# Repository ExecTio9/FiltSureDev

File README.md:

# FiltSure HVAC Monitor

*Internal Project — FiltSure Team*

FiltSure is an IoT-based environmental monitoring system for HVAC systems. It collects real-time environmental data and filter identity information, logging to a cloud service via dual WiFi and LoRa communication.  
The system is designed for reliable field operation and simple installation by HVAC technicians or homeowners.

---

## System Overview

- 📡 Dual Communication: **WiFi** with **LoRa fallback**
- 🌡️ Tracks **Temperature**, **Humidity**, **Pressure**
- 🪪 Identifies Filters via **RFID**
- 🔋 Logs **Battery Voltage** and **Wind Speed**
- 🟢 Displays system health via **RGB LED Diagnostics**
- 🛠️ Designed for **easy installation** inside HVAC units

---

## Architecture

Sensors → ESP32 Sensor Node → WiFi / LoRa → ESP32 Hotspot Gateway → Google Apps Script → Google Sheets (Cloud Logging)

### Sensor Node

- **ESP32-C6 DevKitM-1**
- **BME280** — Temp / Humidity / Pressure
- **MFRC522** — RFID Filter Sensor
- **14-bit ADC** — Battery Monitor
- **12V Brushless Fan** — Wind Speed Sensor
- **RFM95** — LoRa Module
- **RGB LED** — Diagnostics
- **USB** — Power & Diagnostics Mode

### Gateway Node

- **ESP32-C3 or C6**
- **WiFi AP (ESP32 Hotspot)**
- **LoRa Receiver (RFM95)**
- **Google Apps Script Forwarding**
- **Diagnostic Ping Capability**

---

## Suggested Repo Structure

```text
FiltSure-HVAC-Monitor/
├── README.md                 # Project documentation (this file)
├── LICENSE.md                # Internal License
├── docs/                     # Architecture diagrams, setup guides
├── firmware/
│   ├── sensor_node/          # Source code for Sensor Node (ESP32-C6)
│   │   ├── src/
│   │   ├── include/
│   │   ├── platformio.ini    # or arduino config
│   ├── gateway_node/         # Source code for Gateway Node (ESP32-C3/C6)
│   │   ├── src/
│   │   ├── include/
│   │   ├── platformio.ini    # or arduino config
├── google_scripts/           # Google Apps Script for cloud logging
├── hardware/                 # Schematics, PCB files (KiCad)
├── testing/                  # Test scripts, diagnostic tools
└── images/                   # Project images, architecture diagrams

```
Data Fields

| Field             | Description               |
| ----------------- | ------------------------- |
| `id`              | Device ID                 |
| `boot count`      | Power cycle count         |
| `battery voltage` | Battery level (V)         |
| `sensor status`   | Sensor health status      |
| `temperature`     | Temperature in °C         |
| `humidity`        | Relative Humidity (%)     |
| `pressure`        | Pressure (hPa)            |
| `wind speed`      | Derived air flow velocity |
| `rfid`            | Filter RFID Tag UID       |

### Installation Guide For Technicians
- Mount Sensor Node inside HVAC unit (side wall recommended).
- Install Wind Sensor across airflow path.
- Attach RFID Tag to HVAC filter.
- Power the Node via battery or USB.
- Verify Gateway Connection (WiFi pairing).
- Confirm Data Logging in the FiltSure Google Sheet.

### Maintenance
- Replace battery pack periodically (check logged voltage).
- Trigger Diagnostic Mode when servicing units.
- OTA firmware updates via Gateway (WIP).

### Developer Setup
- Prerequisites
  - Arduino IDE or PlatformIO
  - ESP32 Board Support (ESP32-C3, C6)
- Required Libraries:
  - Adafruit_BME280
  - MFRC522
  - RadioHead (RH_RF95)
  - WiFiManager (if used)
  - Google Apps Script URL configured

## Flashing the Node
esptool.py --port COMx --baud 460800 write_flash 0x10000 firmware.bin

## Configuration
Edit these parameters in your code:
```text
#define WIFI_SSID     "ESP32_HOTSPOT"
#define WIFI_PASS     "FiltSure_Rules"
#define RF95_FREQ     915.0
#define NODE_ID       X
#define DEST_ID       Y
#define GOOGLE_SHEET_URL "https://script.google.com/macros/..."
```

# Diagnostic Mode (RGB LED)
##Trigger:
USB Plug-In
GPIO Wake Pin
LoRa Ping from Gateway

## LED Codes
### Sensor Status Pulse
Color	Meaning
- Green	All sensors working
- Yellow	Only BME280 working
- Blue	Only RFID working
- Red	Neither sensor working

### Battery Level Pulse
Color	Meaning
- Green	> 75%
- Yellow	40–75%
- Red	< 40%

### Communication Mode Pulse
Color	Meaning
Green	WiFi active
Blue	LoRa active
Red	Offline / No communication

# Roadmap / TODO
- Wind Speed calibration improvements
- Dynamic LoRa Node ID assignment
- Full OTA update pipeline via Gateway
- Additional sensor support (VOC, PM2.5)
- Expand Google Sheets logging format

# Internal Links
- [FiltSure_Watch monitoring sheet](https://docs.google.com/spreadsheets/d/1jLbKlstPxHlD7kHZhQn0Z-8PDUdkm7ZQxHZjDr8VWqw/edit?gid=1254838656#gid=1254838656)
- [Google App Script Code](https://script.google.com/home/projects/1kvNN4aTYOBjVC-IF9PAhh4AED5QBl2EmA35dcaVsej_4SW3x39zN_HsJ/edit)
- [Documentation Guide](docs\FiltSure_HVAC_Monitor_Guide_v1_FULL_Draft_v2.docx)

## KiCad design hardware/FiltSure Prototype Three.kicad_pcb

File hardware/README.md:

# Hardware Files — FiltSure HVAC Monitor

This folder contains the hardware design files for the FiltSure HVAC Monitor system.

## Purpose

- Provide schematics and PCB layouts for both Sensor Node and Gateway Node hardware
- Enable hardware review, fabrication, and future revisions

## Current Contents

### Sensor Node

- `Sensor_Node.sch` — KiCad schematic for Sensor Node
- `Sensor_Node.kicad_pcb` — KiCad PCB layout for Sensor Node

### Gateway Node

- `Gateway_Node.sch` — KiCad schematic for Gateway Node
- `Gateway_Node.kicad_pcb` — KiCad PCB layout for Gateway Node

## Notes

- All files are created using **KiCad** (version 9.0+ recommended)
- Schematics include:
  - Power supply & battery monitor
  - Sensor interfaces (BME280, MFRC522, Wind Speed Fan)
  - RGB LED driver
  - LoRa module interface (RFM95)
- PCB layouts designed for easy assembly & field serviceability

## Usage

- Schematics can be viewed and edited in KiCad
- PCB files can be exported for fabrication:
  - Gerber files
  - Drill files
  - BOM (Bill of Materials)
- Recommended to generate Gerbers with KiCad default plot settings

## Related Docs

- FiltSure Guide — Hardware BOM section
- FiltSure Power Budget Spreadsheet (linked in Guide)

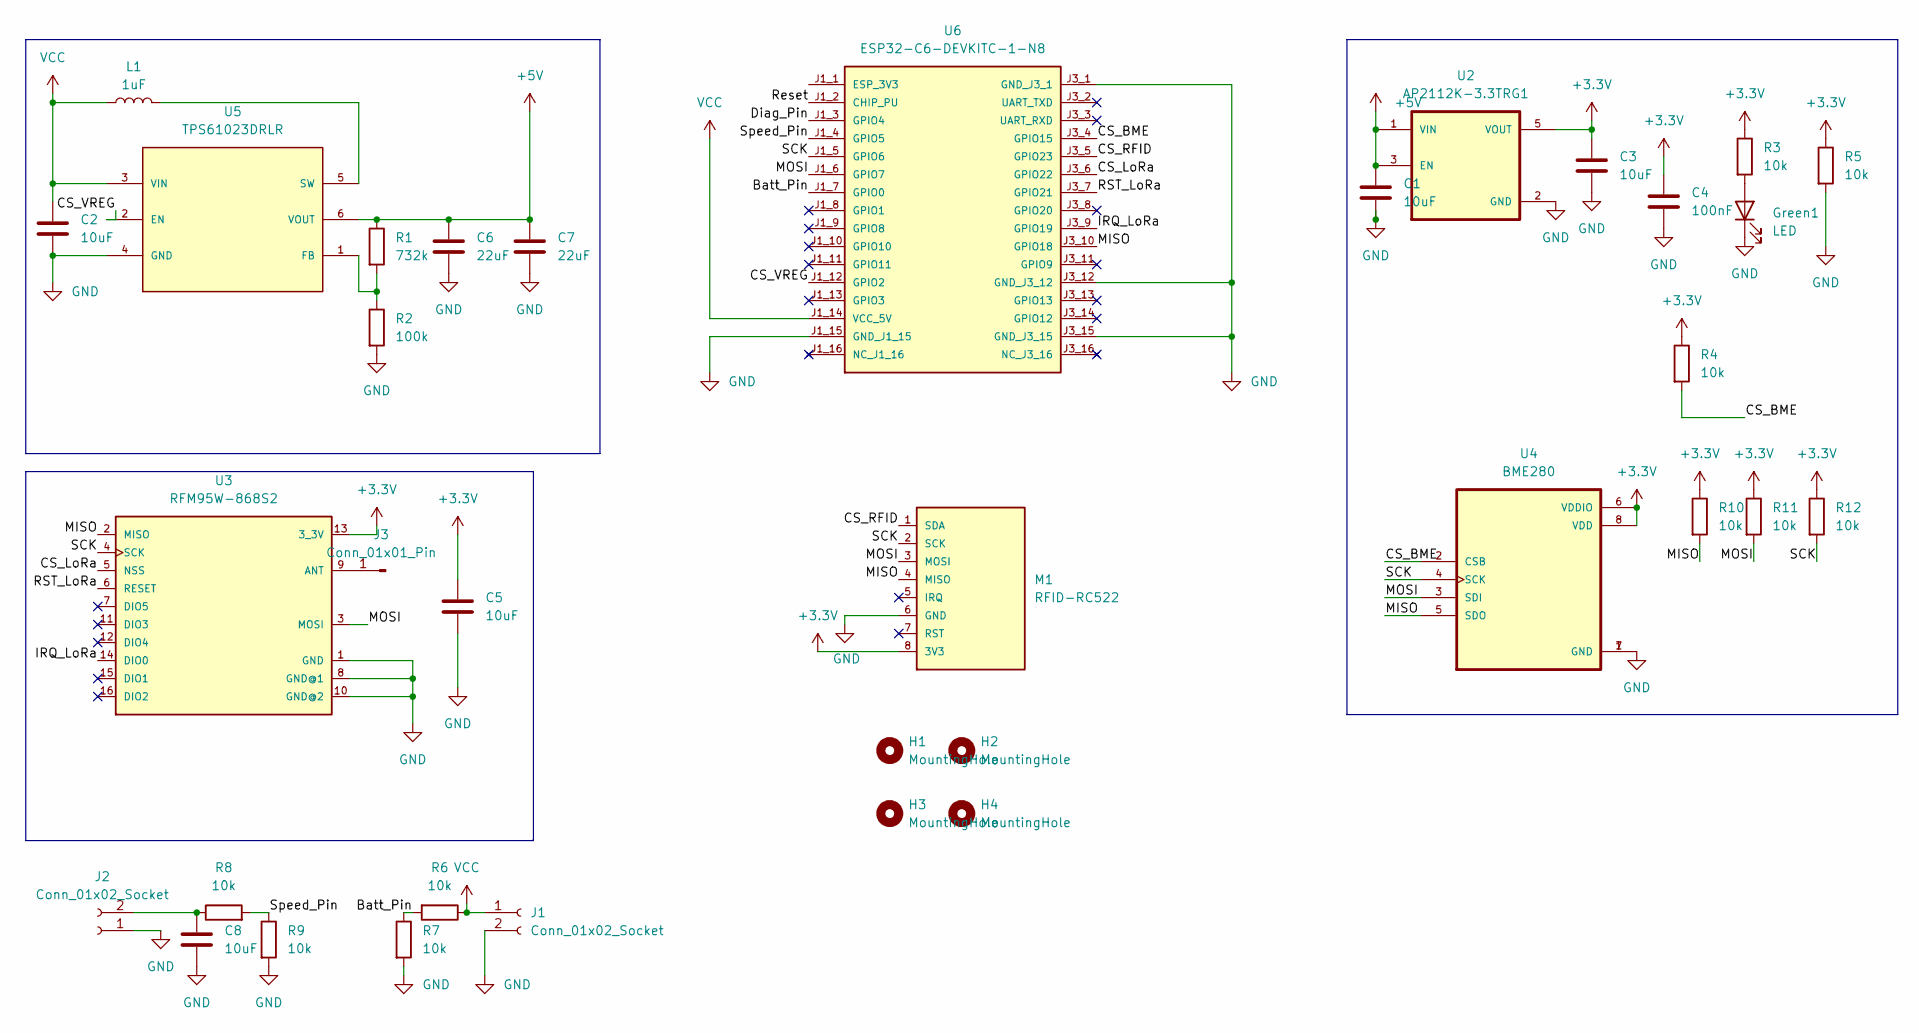
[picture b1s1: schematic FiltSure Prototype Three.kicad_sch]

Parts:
C1, C2, C3, C5, C8: 10uF; C_0603_1608Metric
C4: 100nF; C_0603_1608Metric
C6, C7: 22uF; C_0603_1608Metric
Green1: LED; C_0603_1608Metric
H1, H2, H3, H4: MountingHole; MountingHole_2.7mm
J1, J2: Conn_01x02_Socket; PinHeader_1x02_P2.54mm_Vertical
J3: Conn_01x01_Pin; PinHeader_1x01_P1.00mm_Vertical
L1: 1uF; L_Neosid_SM-PIC0512H
M1: RFID-RC522; MPN RFID-RC522
R1: 732k; C_0603_1608Metric
R2: 100k; C_0603_1608Metric
R3, R10, R11, R12: 10k; R_0603_1608Metric
R4, R5, R6, R7, R8, R9: 10k; C_0603_1608Metric
U2: AP2112K-3.3TRG1; SOT95P285X140-5N; PARTREV 2-2
U3: RFM95W-868S2; XCVR_RFM95W-868S2
U4: BME280; PSON65P250X250X100-8N
U5: TPS61023DRLR; DRL0006A; PARTNUMBER TPS61023DRL
U6: ESP32-C6-DEVKITC-1-N8; MODULE_ESP32-C6-DEVKITC-1-N8; PARTREV 1.3

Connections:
+3.3V: C3.1, C4.1, C5.1, M1.8 (3V3), R3.1, R4.1, R5.1, R10.1, R11.1, R12.1, U2.5 (VOUT), U3.13 (3_3V), U4.6 (VDDIO), U4.8 (VDD)
+5V: C1.1, C6.1, C7.1, R1.1, U2.1 (VIN), U2.3 (EN), U5.6 (VOUT)
/Batt_Pin: R6.2, R7.1, U6.J1_7 (GPIO0)
/CS_BME: R4.2, U4.2 (CSB), U6.J3_4 (GPIO15)
/CS_LoRa: U3.5 (NSS), U6.J3_6 (GPIO22)
/CS_RFID: M1.1 (SDA), U6.J3_5 (GPIO23)
/CS_VREG: U5.2 (EN), U6.J1_12 (GPIO2)
/Diag_Pin: U6.J1_3 (GPIO4)
/IRQ_LoRa: U3.14 (DIO0), U6.J3_9 (GPIO19)
/MISO: M1.4 (MISO), R10.2, U3.2 (MISO), U4.5 (SDO), U6.J3_10 (GPIO18)
/MOSI: M1.3 (MOSI), R11.2, U3.3 (MOSI), U4.3 (SDI), U6.J1_6 (GPIO7)
/RST_LoRa: U3.6 (RESET), U6.J3_7 (GPIO21)
/Reset: U6.J1_2 (CHIP_PU)
/SCK: M1.2 (SCK), R12.2, U3.4 (SCK), U4.4 (SCK), U6.J1_5 (GPIO6)
/Speed_Pin: R8.2, R9.1, U6.J1_4 (GPIO5)
GND: C1.2, C2.2, C3.2, C4.2, C5.2, C6.2, C7.2, C8.2, Green1.1 (K), J1.2, J2.1, M1.6 (GND), R2.2, R5.2, R7.2, R9.2, U2.2 (GND), U3.1 (GND), U3.8 (GND@1), U3.10 (GND@2), U4.1 (GND), U4.7 (GND), U5.4 (GND), U6.J1_15 (GND_J1_15), U6.J3_1 (GND_J3_1), U6.J3_12 (GND_J3_12), U6.J3_15 (GND_J3_15); also elsewhere on the board
unnamed 16: Green1.2 (A), R3.2; also elsewhere on the board
unnamed: C8.1, J2.2, R8.1
unnamed: J3.1, U3.9 (ANT)
unnamed: R1.2, R2.1, U5.1 (FB)
unnamed: L1.2, U5.5 (SW)
VCC: C2.1, J1.1, L1.1, R6.1, U5.3 (VIN), U6.J1_14 (VCC_5V)

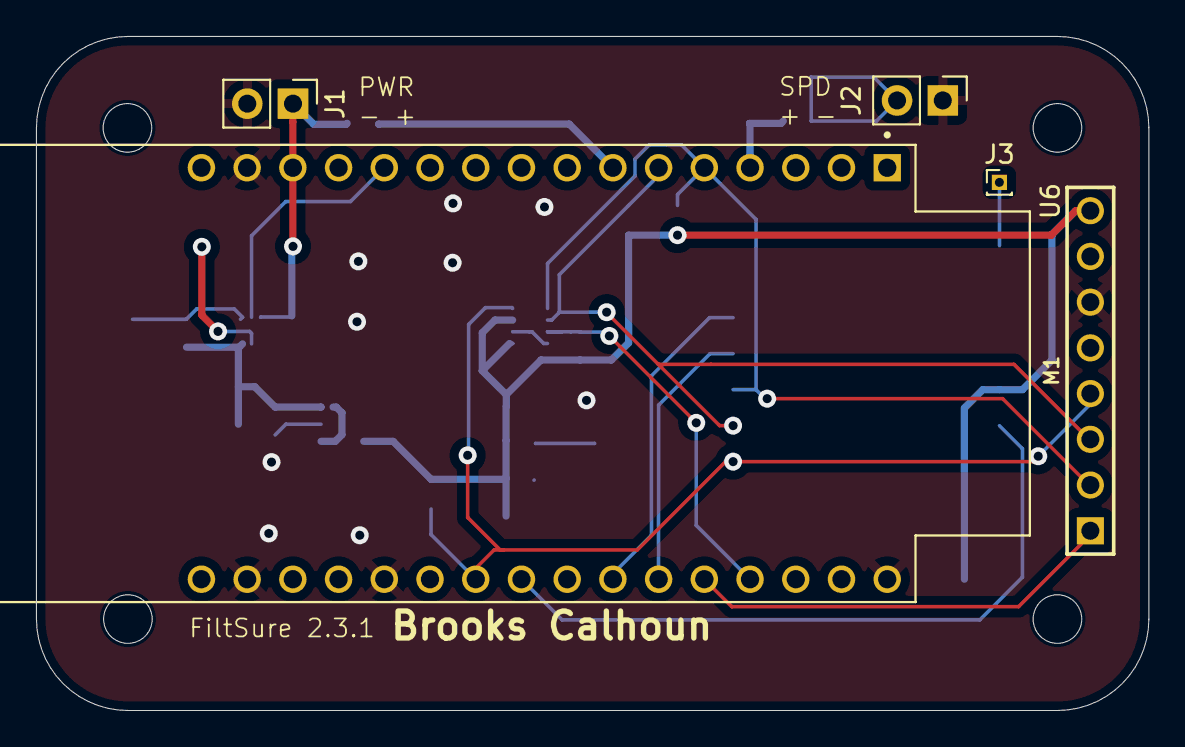
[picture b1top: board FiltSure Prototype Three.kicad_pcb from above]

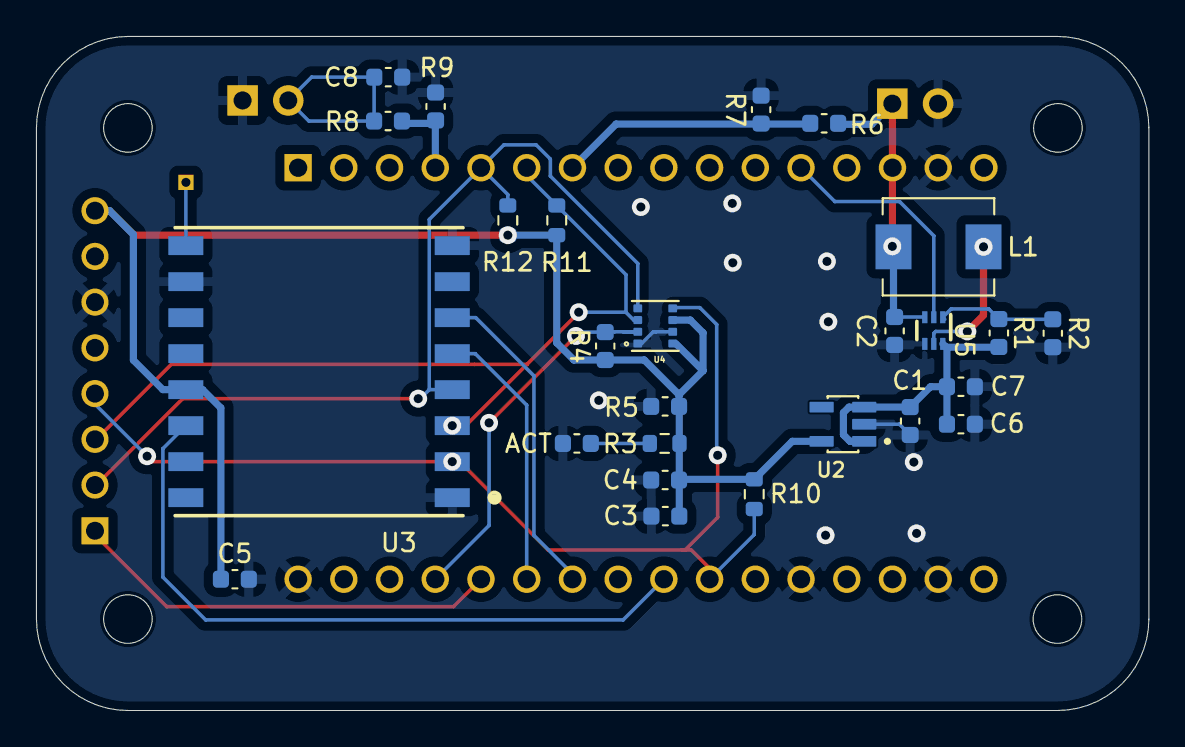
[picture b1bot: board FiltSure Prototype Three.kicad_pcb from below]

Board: 2 copper layers, 61.8 x 37.4 mm, 35 parts (26 on the bottom side), 20 nets.

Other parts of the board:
ACT: LED; C_0603_1608Metric

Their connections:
GND: ACT.1 (K); also elsewhere on the board
unnamed 16: ACT.2 (A); also elsewhere on the board

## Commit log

2025-06-13 Rename Released.md to RELEASE.md
2025-06-13 add README laceholders to project folders
2025-06-13 update README.md for Hardware folder
2025-06-13 Add Sensor node KiCad Files
2025-06-13 add full .gitignore for project
2025-06-13 Add Project_Process.md template
2025-06-13 Add Architecture_diagram.png & XML to images
2025-06-20 Added comments to esp32_c6_sensor_fusion_full.ino file
2025-07-25 Add files via upload
    Separate BME and RFID codes
2026-04-17 final copy commited by creator
    fixed RFID and Power pin issues, changed wifi name "FiltSure-Setup" to "AirFlowIQ-Setup"
2026-04-17 Last Made PCB
    Fixed Power Regulation issues
